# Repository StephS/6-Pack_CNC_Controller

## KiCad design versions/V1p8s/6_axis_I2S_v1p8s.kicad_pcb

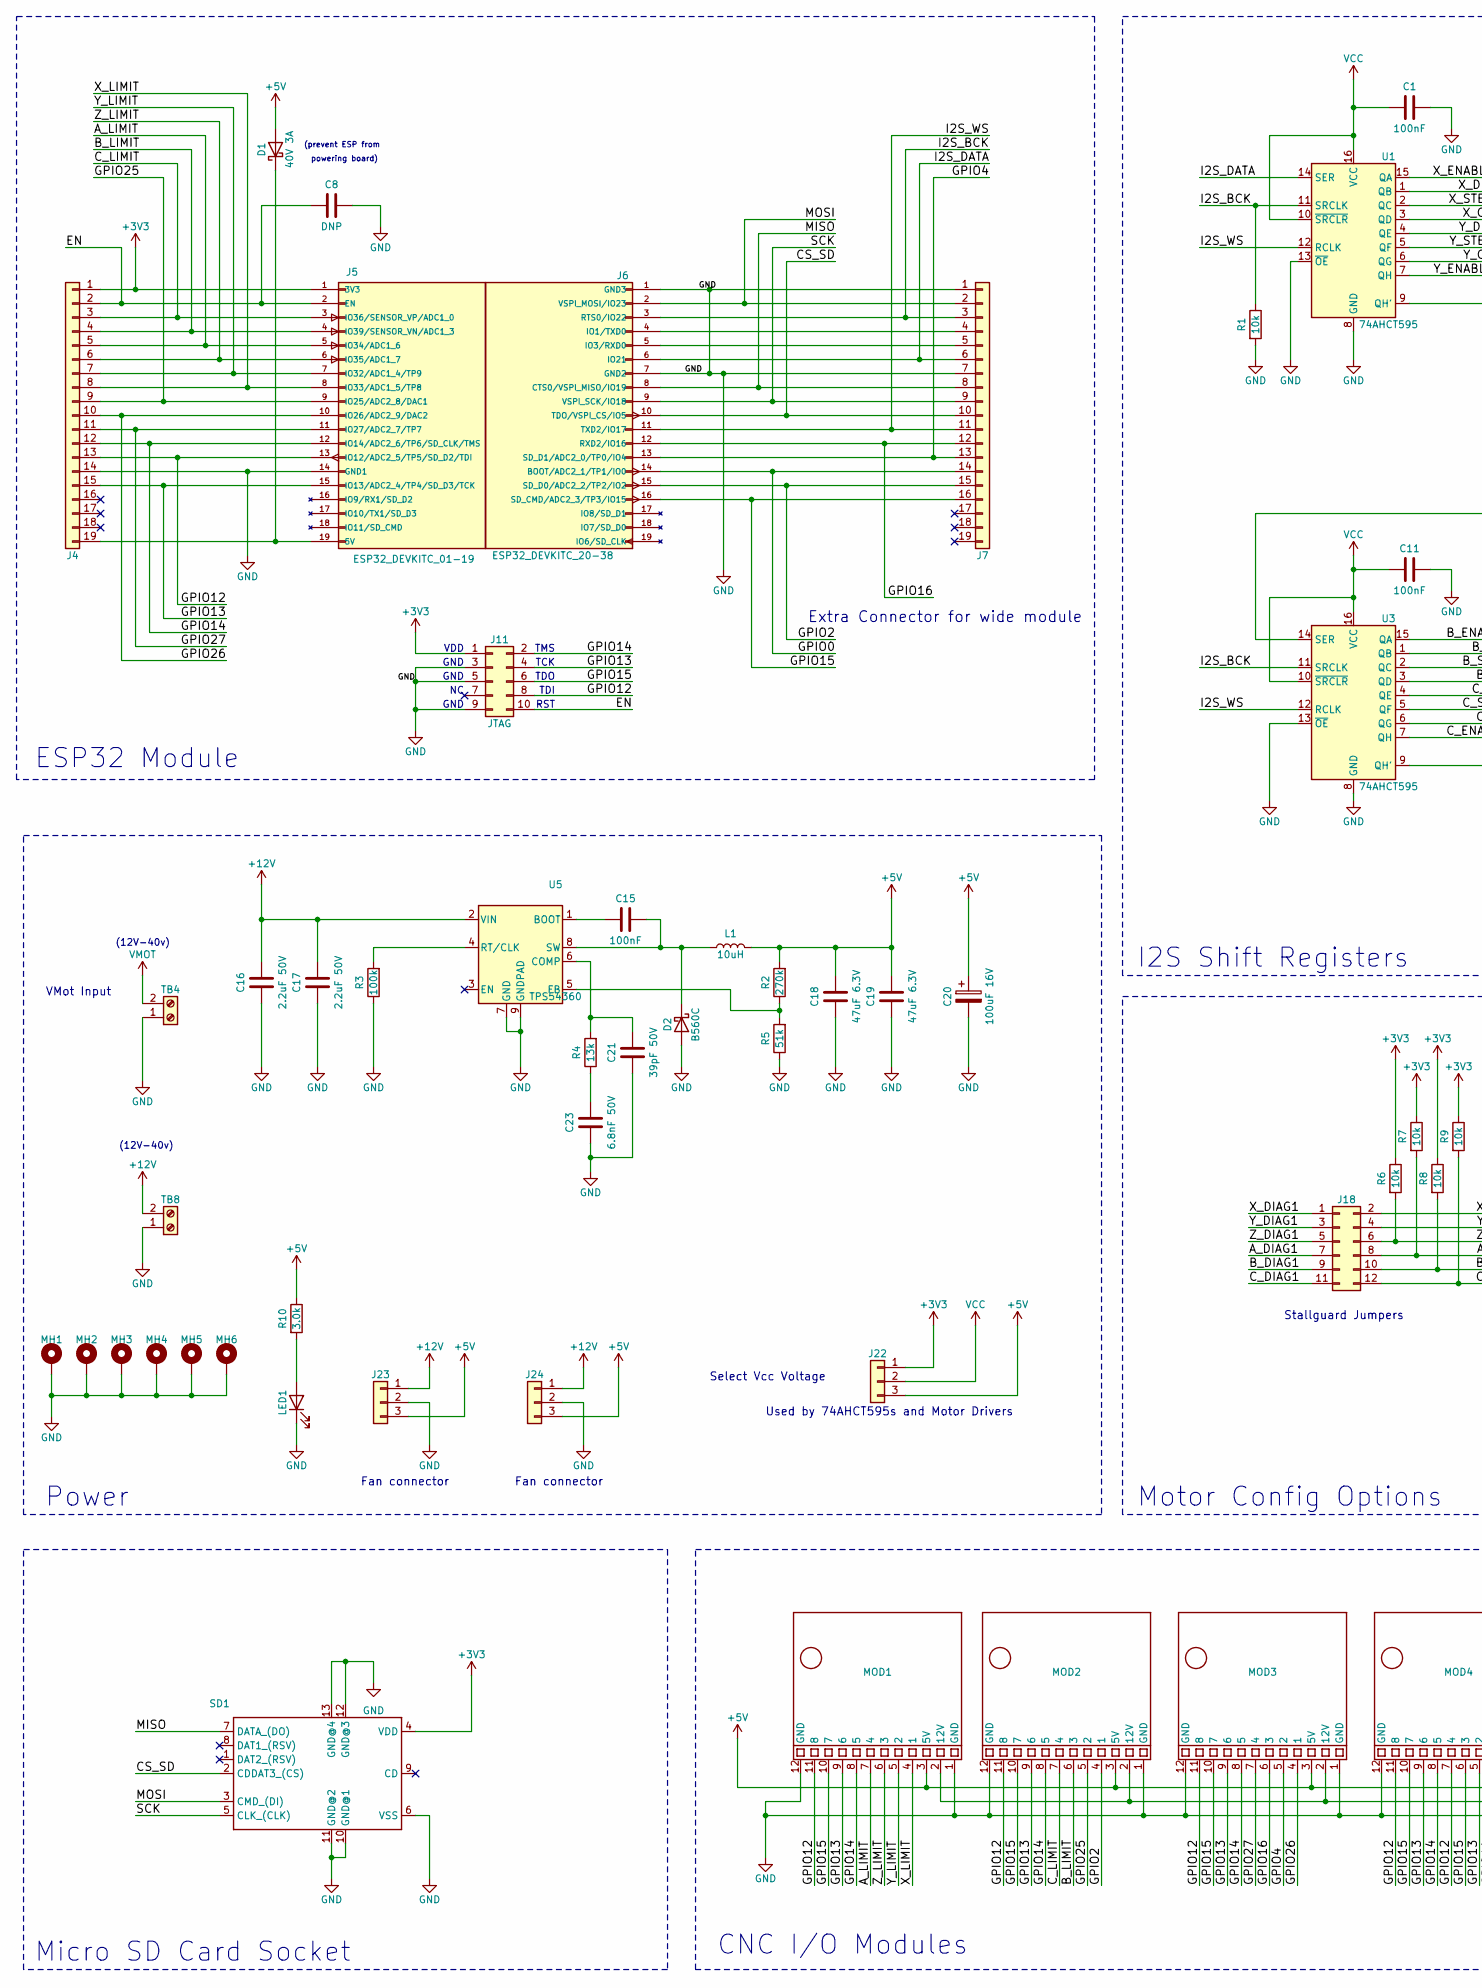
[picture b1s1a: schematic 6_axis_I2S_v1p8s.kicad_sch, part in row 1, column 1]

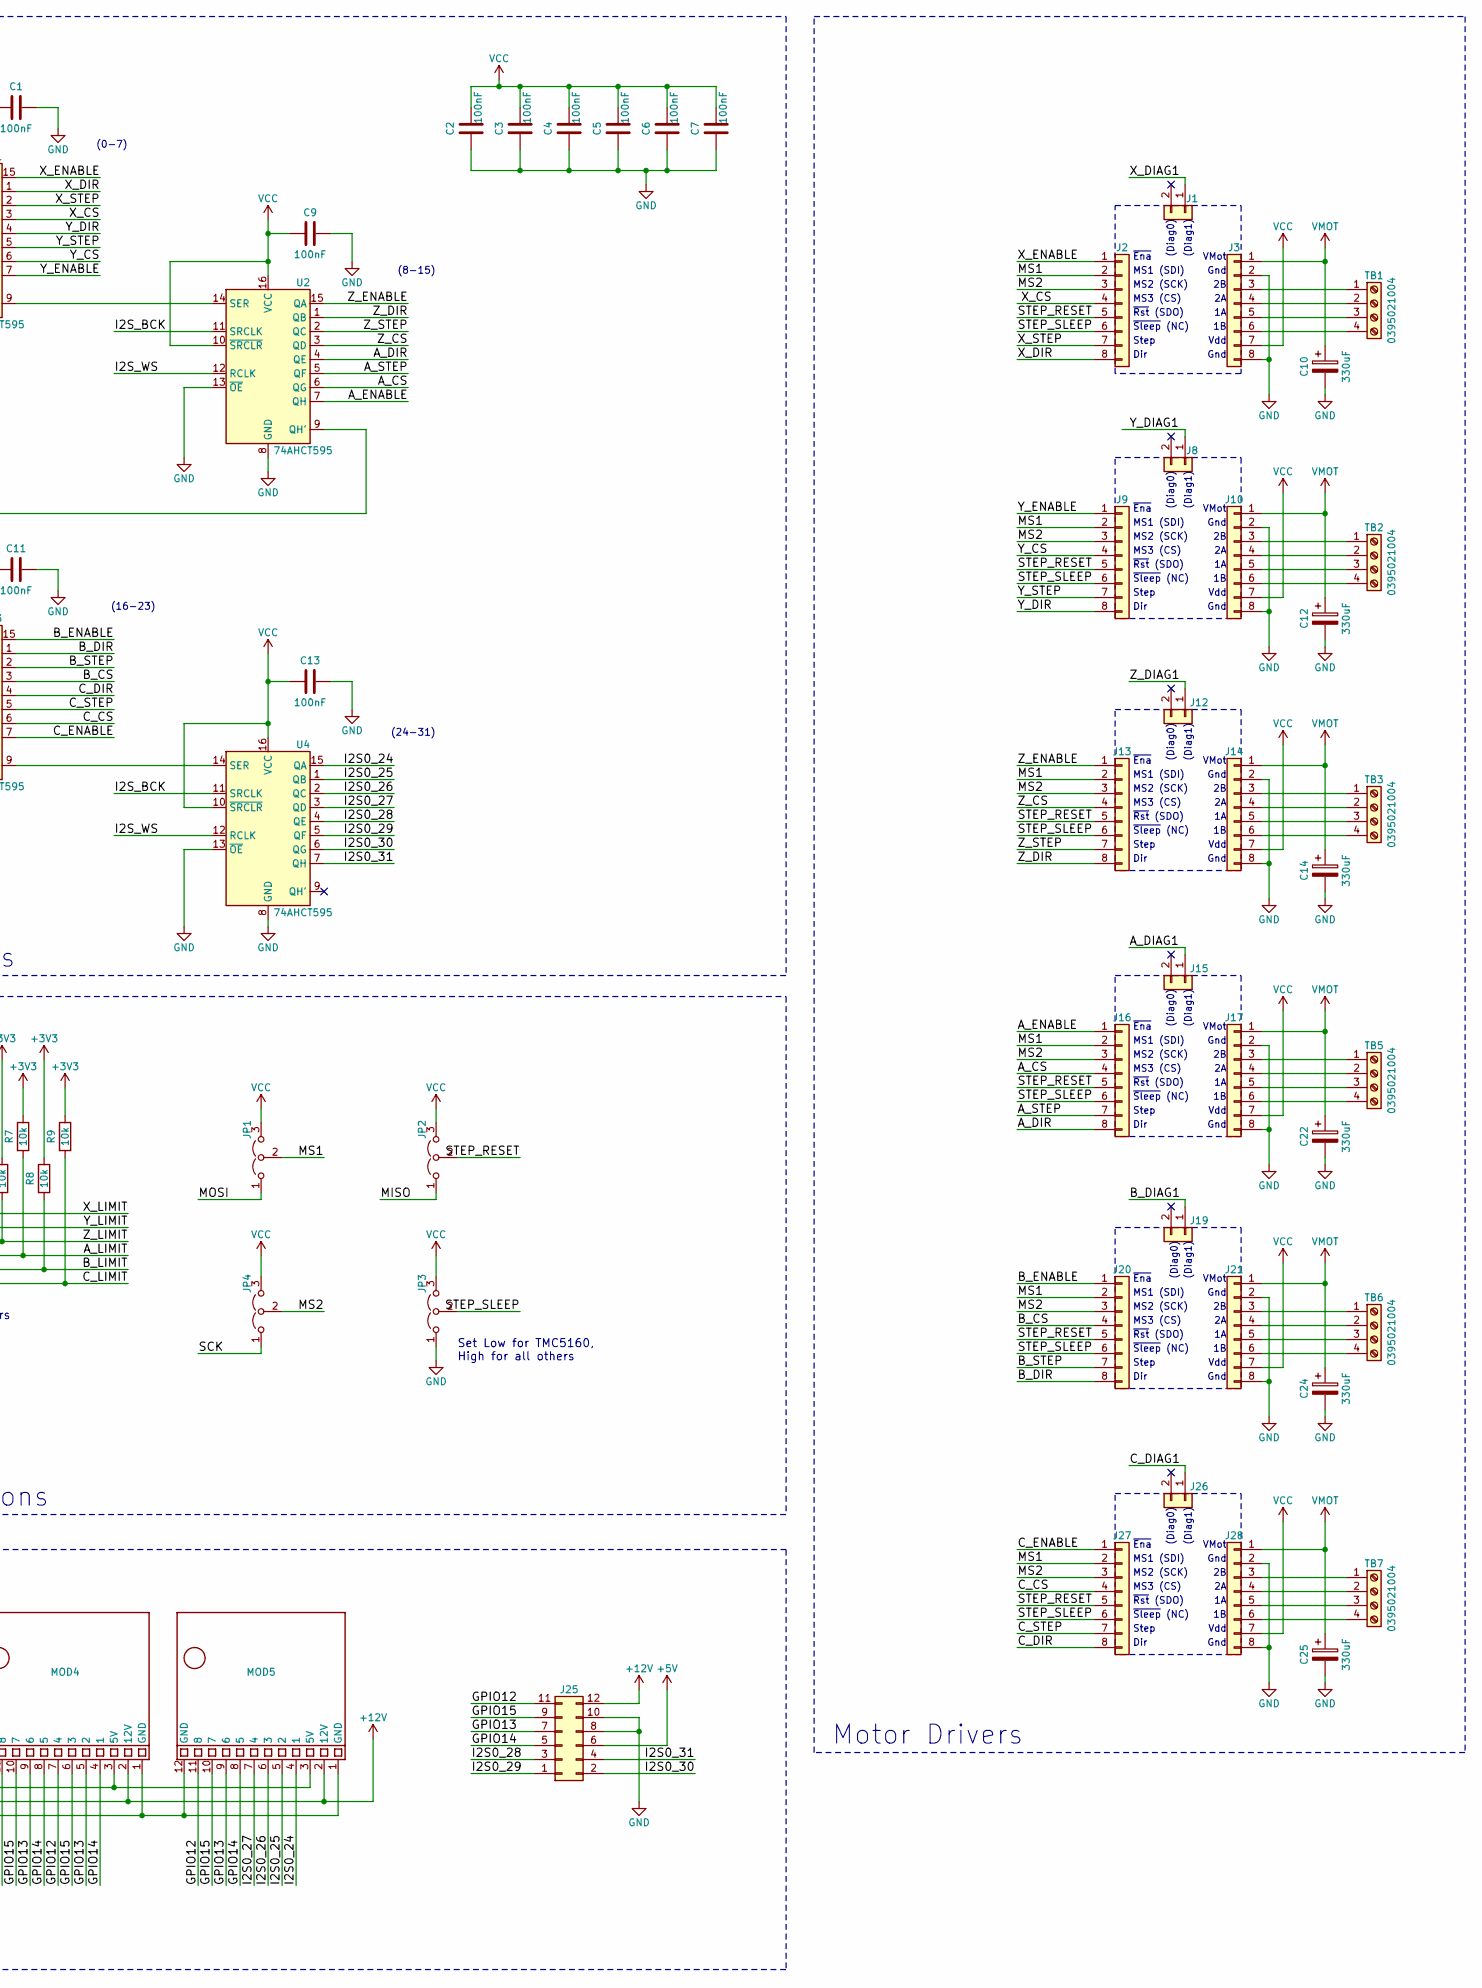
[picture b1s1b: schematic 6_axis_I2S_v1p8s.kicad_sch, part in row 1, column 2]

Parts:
C1, C2, C3, C4, C5, C6, C7, C9, C11, C13, C15: 100nF; C_0402_1005Metric_Pad0.74x0.62mm_HandSolder
C8: DNP; C_1206_3216Metric_Pad1.42x1.75mm_HandSolder
C10, C12, C14, C22, C24, C25: 330uF; C_Elec_10x10.2
C16, C17: 2.2uF 50V; C_0805_2012Metric
C18, C19: 47uF 6.3V; C_0805_2012Metric
C20: 100uF 16V; CP_Elec_6.3x9.9
C21: 39pF 50V; C_0402_1005Metric
C23: 6.8nF 50V; C_0402_1005Metric
D1: 40V 3A; D_SMA
D2: B560C; D_SMC
J1, J8, J12, J15, J19, J26: 2 Pos; PinSocket_1x02_P2.54mm_Vertical
J2, J3, J9, J10, J13, J14, J16, J17, J20, J21, J27, J28: 8S; PinSocket_1x08_P2.54mm_Vertical
J4, J7: 19S; PinSocket_1x19_P2.54mm_Vertical
J5: ESP32_DEVKITC_01-19; PinSocket_1x19_P2.54mm_Vertical
J6: ESP32_DEVKITC_20-38; PinSocket_1x19_P2.54mm_Vertical
J11: JTAG; IDC-Header_2x05_P2.54mm_Vertical
J18: 6S; PinHeader_2x06_P2.54mm_Vertical
J22, J23, J24: 3P; PinHeader_1x03_P2.54mm_Vertical
J25: 6S; PinSocket_2x06_P2.54mm_Horizontal
JP1, JP2, JP3, JP4: 3P; PinHeader_1x03_P2.54mm_Vertical
L1: 10uH; L_Sunlord_MWSA0503_5.4x5.2mm; Part N MWSA0503S-100MT
LED1: GRN; LED_0805_2012Metric_Castellated
MH1, MH2, MH3, MH4, MH5, MH6: MOUNTING_HOLE_M3.7; MountingHole_3.5mm_Pad_TopBottom
MOD1, MOD2, MOD3, MOD4, MOD5: 1x12 Socket; CNC_ModuleSocket_1x12_P2.54mm
R1, R6, R7, R8, R9: 10k; R_0402_1005Metric
R2: 270k; R_0402_1005Metric
R3: 100k; R_0402_1005Metric
R4: 13k; R_0402_1005Metric
R5: 51k; R_0402_1005Metric
R10: 3.0k; R_0603_1608Metric_Pad0.98x0.95mm_HandSolder
SD1: Micro SD; HRO_ELEC-TF-01A
TB1, TB2, TB3, TB5, TB6, TB7: 0395021004; TerminalBlock_Molex_0395021004_1x04_P3.50mm_Horizontal
TB4, TB8: 2 Pos; TerminalBlock_Phoenix_MKDS-1,5-2_1x02_P5.00mm_Horizontal
U1, U2, U3, U4: 74AHCT595; SOIC-16_3.9x9.9mm_P1.27mm
U5: TPS54360; TI_SO-PowerPAD-8

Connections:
+3V3: J4.1, J5.1 (3V3), J11.1, J22.1, R6.1, R7.1, R8.1, R9.1, SD1.4 (VDD)
+5V: C18.2, C19.2, C20.1, D1.2 (A), J22.3, J23.3, J24.3, J25.6, L1.2, MOD1.3 (5V), MOD2.3 (5V), MOD3.3 (5V), MOD4.3 (5V), MOD5.3 (5V), R2.2, R10.1
+12V: C16.2, C17.2, J23.1, J24.1, J25.12, MOD1.2 (12V), MOD2.2 (12V), MOD3.2 (12V), MOD4.2 (12V), MOD5.2 (12V), TB8.2, U5.2 (VIN)
/A_CS: J16.4, U2.6 (QG)
/A_DIAG1: J15.1, J18.7
/A_DIR: J16.8, U2.4 (QE)
/A_ENABLE: J16.1, U2.7 (QH)
/A_LIMIT: J4.5, J5.5 (IO34/ADC1_6), J18.8, MOD1.7 (4), R7.2
/A_STEP: J16.7, U2.5 (QF)
/B_CS: J20.4, U3.3 (QD)
/B_DIAG1: J18.9, J19.1
/B_DIR: J20.8, U3.1 (QB)
/B_ENABLE: J20.1, U3.15 (QA)
/B_LIMIT: J4.4, J5.4 (IO39/SENSOR_VN/ADC1_3), J18.10, MOD2.6 (3), R8.2
/B_STEP: J20.7, U3.2 (QC)
/CS_SD: J6.10 (TDO/VSPI_CS/IO5), J7.10, SD1.2 (CDDAT3_(CS))
/C_CS: J27.4, U3.6 (QG)
/C_DIAG1: J18.11, J26.1
/C_DIR: J27.8, U3.4 (QE)
/C_ENABLE: J27.1, U3.7 (QH)
/C_LIMIT: J4.3, J5.3 (IO36/SENSOR_VP/ADC1_0), J18.12, MOD2.7 (4), R9.2
/C_STEP: J27.7, U3.5 (QF)
/EN: C8.1, J4.2, J5.2 (EN), J11.10
/GPIO0: J6.14 (BOOT/ADC2_1/TP1/IO0), J7.14
/GPIO2: J6.15 (SD_D0/ADC2_2/TP2/IO2), J7.15, MOD2.4 (1)
/GPIO4: J6.13 (SD_D1/ADC2_0/TP0/IO4), J7.13, MOD3.5 (2)
/GPIO12: J4.13, J5.13 (IO12/ADC2_5/TP5/SD_D2/TDI), J11.8, J25.11, MOD1.11 (8), MOD2.11 (8), MOD3.11 (8), MOD4.7 (4), MOD4.11 (8), MOD5.11 (8)
/GPIO13: J4.15, J5.15 (IO13/ADC2_4/TP4/SD_D3/TCK), J11.4, J25.7, MOD1.9 (6), MOD2.9 (6), MOD3.9 (6), MOD4.5 (2), MOD4.9 (6), MOD5.9 (6)
/GPIO14: J4.12, J5.12 (IO14/ADC2_6/TP6/SD_CLK/TMS), J11.2, J25.5, MOD1.8 (5), MOD2.8 (5), MOD3.8 (5), MOD4.4 (1), MOD4.8 (5), MOD5.8 (5)
/GPIO15: J6.16 (SD_CMD/ADC2_3/TP3/IO15), J7.16, J11.6, J25.9, MOD1.10 (7), MOD2.10 (7), MOD3.10 (7), MOD4.6 (3), MOD4.10 (7), MOD5.10 (7)
/GPIO16: J6.12 (RXD2/IO16), J7.12, MOD3.6 (3)
/GPIO25: J4.9, J5.9 (IO25/ADC2_8/DAC1), MOD2.5 (2)
/GPIO26: J4.10, J5.10 (IO26/ADC2_9/DAC2), MOD3.4 (1)
/GPIO27: J4.11, J5.11 (IO27/ADC2_7/TP7), MOD3.7 (4)
/I2S0_24: MOD5.4 (1), U4.15 (QA)
/I2S0_25: MOD5.5 (2), U4.1 (QB)
/I2S0_26: MOD5.6 (3), U4.2 (QC)
/I2S0_27: MOD5.7 (4), U4.3 (QD)
/I2S0_28: J25.3, U4.4 (QE)
/I2S0_29: J25.1, U4.5 (QF)
/I2S0_30: J25.2, U4.6 (QG)
/I2S0_31: J25.4, U4.7 (QH)
/I2S_BCK: J6.3 (RTS0/IO22), J7.3, R1.1, U1.11 (SRCLK), U2.11 (SRCLK), U3.11 (SRCLK), U4.11 (SRCLK)
/I2S_DATA: J6.6 (IO21), J7.6, U1.14 (SER)
/I2S_WS: J6.11 (TXD2/IO17), J7.11, U1.12 (RCLK), U2.12 (RCLK), U3.12 (RCLK), U4.12 (RCLK)
/MISO: J6.8 (CTS0/VSPI_MISO/IO19), J7.8, JP2.1 (A), SD1.7 (DATA_(DO))
/MOSI: J6.2 (VSPI_MOSI/IO23), J7.2, JP1.1 (A), SD1.3 (CMD_(DI))
/MS1: J2.2, J9.2, J13.2, J16.2, J20.2, J27.2, JP1.2 (C)
/MS2: J2.3, J9.3, J13.3, J16.3, J20.3, J27.3, JP4.2 (C)
/SCK: J6.9 (VSPI_SCK/IO18), J7.9, JP4.1 (A), SD1.5 (CLK_(CLK))
/STEP_RESET: J2.5, J9.5, J13.5, J16.5, J20.5, J27.5, JP2.2 (C)
/STEP_SLEEP: J2.6, J9.6, J13.6, J16.6, J20.6, J27.6, JP3.2 (C)
/X_CS: J2.4, U1.3 (QD)
/X_DIAG1: J1.1, J18.1
/X_DIR: J2.8, U1.1 (QB)
/X_ENABLE: J2.1, U1.15 (QA)
/X_LIMIT: J4.8, J5.8 (IO33/ADC1_5/TP8), J18.2, MOD1.4 (1)
/X_STEP: J2.7, U1.2 (QC)
/Y_CS: J9.4, U1.6 (QG)
/Y_DIAG1: J8.1, J18.3
/Y_DIR: J9.8, U1.4 (QE)
/Y_ENABLE: J9.1, U1.7 (QH)
/Y_LIMIT: J4.7, J5.7 (IO32/ADC1_4/TP9), J18.4, MOD1.5 (2)
/Y_STEP: J9.7, U1.5 (QF)
/Z_CS: J13.4, U2.3 (QD)
/Z_DIAG1: J12.1, J18.5
/Z_DIR: J13.8, U2.1 (QB)
/Z_ENABLE: J13.1, U2.15 (QA)
/Z_LIMIT: J4.6, J5.6 (IO35/ADC1_7), J18.6, MOD1.6 (3), R6.2
/Z_STEP: J13.7, U2.2 (QC)
GND: C1.2, C2.1, C3.1, C4.1, C5.1, C6.1, C7.1, C8.2, C9.2, C10.2, C11.2, C12.2, C13.2, C14.2, C16.1, C17.1, C18.1, C19.1, C20.2, C21.1, C22.2, C23.1, C24.2, C25.2, D2.2 (A), J3.2, J3.8, J4.14, J5.14 (GND1), J6.1 (GND3), J6.7 (GND2), J7.1, J7.7, J10.2, J10.8, J11.3, J11.5, J11.9, J14.2, J14.8, J17.2, J17.8, J21.2, J21.8, J23.2, J24.2, J25.8, J25.10, J28.2, J28.8, JP3.1 (A), LED1.1 (K), MH1.1, MH2.1, MH3.1, MH4.1, MH5.1, MH6.1, MOD1.1 (GND), MOD1.12 (GND), MOD2.1 (GND), MOD2.12 (GND), MOD3.1 (GND), MOD3.12 (GND), MOD4.1 (GND), MOD4.12 (GND), MOD5.1 (GND), MOD5.12 (GND), R1.2, R3.1, R5.1, SD1.6 (VSS), SD1.10 (GND@1), SD1.11 (GND@2), SD1.12 (GND@3), SD1.13 (GND@4), TB4.1, TB8.1, U1.8 (GND), U1.13 (~OE), U2.8 (GND), U2.13 (~OE), U3.8 (GND), U3.13 (~OE), U4.8 (GND), U4.13 (~OE), U5.7 (GND), U5.9 (GNDPAD)
unnamed: C15.1, U5.1 (BOOT)
unnamed: C15.2, D2.1 (K), L1.1, U5.8 (SW)
unnamed: C21.2, R4.2, U5.6 (COMP)
unnamed: C23.2, R4.1
unnamed: D1.1 (K), J4.19, J5.19 (5V)
unnamed: J3.3, TB1.1
unnamed: J3.4, TB1.2
unnamed: J3.5, TB1.3
unnamed: J3.6, TB1.4
unnamed: J6.4 (IO1/TXD0), J7.4
unnamed: J6.5 (IO3/RXD0), J7.5
unnamed: J10.3, TB2.1
unnamed: J10.4, TB2.2
unnamed: J10.5, TB2.3
unnamed: J10.6, TB2.4
unnamed: J14.3, TB3.1
unnamed: J14.4, TB3.2
unnamed: J14.5, TB3.3
unnamed: J14.6, TB3.4
unnamed: J17.3, TB5.1
unnamed: J17.4, TB5.2
unnamed: J17.5, TB5.3
unnamed: J17.6, TB5.4
unnamed: J21.3, TB6.1
unnamed: J21.4, TB6.2
unnamed: J21.5, TB6.3
unnamed: J21.6, TB6.4
unnamed: J28.3, TB7.1
unnamed: J28.4, TB7.2
unnamed: J28.5, TB7.3
unnamed: J28.6, TB7.4
unnamed: LED1.2 (A), R10.2
unnamed: R2.1, R5.2, U5.5 (FB)
unnamed: R3.2, U5.4 (RT/CLK)
unnamed: U1.9 (QH'), U2.14 (SER)
unnamed: U2.9 (QH'), U3.14 (SER)
unnamed: U3.9 (QH'), U4.14 (SER)
VCC: C1.1, C2.2, C3.2, C4.2, C5.2, C6.2, C7.2, C9.1, C11.1, C13.1, J3.7, J10.7, J14.7, J17.7, J21.7, J22.2, J28.7, JP1.3 (B), JP2.3 (B), JP3.3 (B), JP4.3 (B), U1.10 (~SRCLR), U1.16 (VCC), U2.10 (~SRCLR), U2.16 (VCC), U3.10 (~SRCLR), U3.16 (VCC), U4.10 (~SRCLR), U4.16 (VCC)
VMOT: C10.1, C12.1, C14.1, C22.1, C24.1, C25.1, J3.1, J10.1, J14.1, J17.1, J21.1, J28.1, TB4.2

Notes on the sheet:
Stallguard Jumpers
VMot
MS3 (CS)
TDO
~{Sleep} (NC)
MS1 (SDI)
(12V-40v)
MS2 (SCK)
~{Ena}
GND
~{Rst} (SDO)
Dir
Step
Gnd
(Diag0)
(Diag1)
(prevent ESP from
TMS
Vdd
Extra Connector for wide module
ESP32 Module
(16-23)
Select Vcc Voltage
(0-7)
Power
RST
Micro SD Card Socket
Used by 74AHCT595s and Motor Drivers
powering board)
I2S Shift Registers
(8-15)
TCK
Fan connector
Motor Drivers
(24-31)
TDI
Motor Config Options
VDD
Set Low for TMC5160, High for all others
CNC I/O Modules

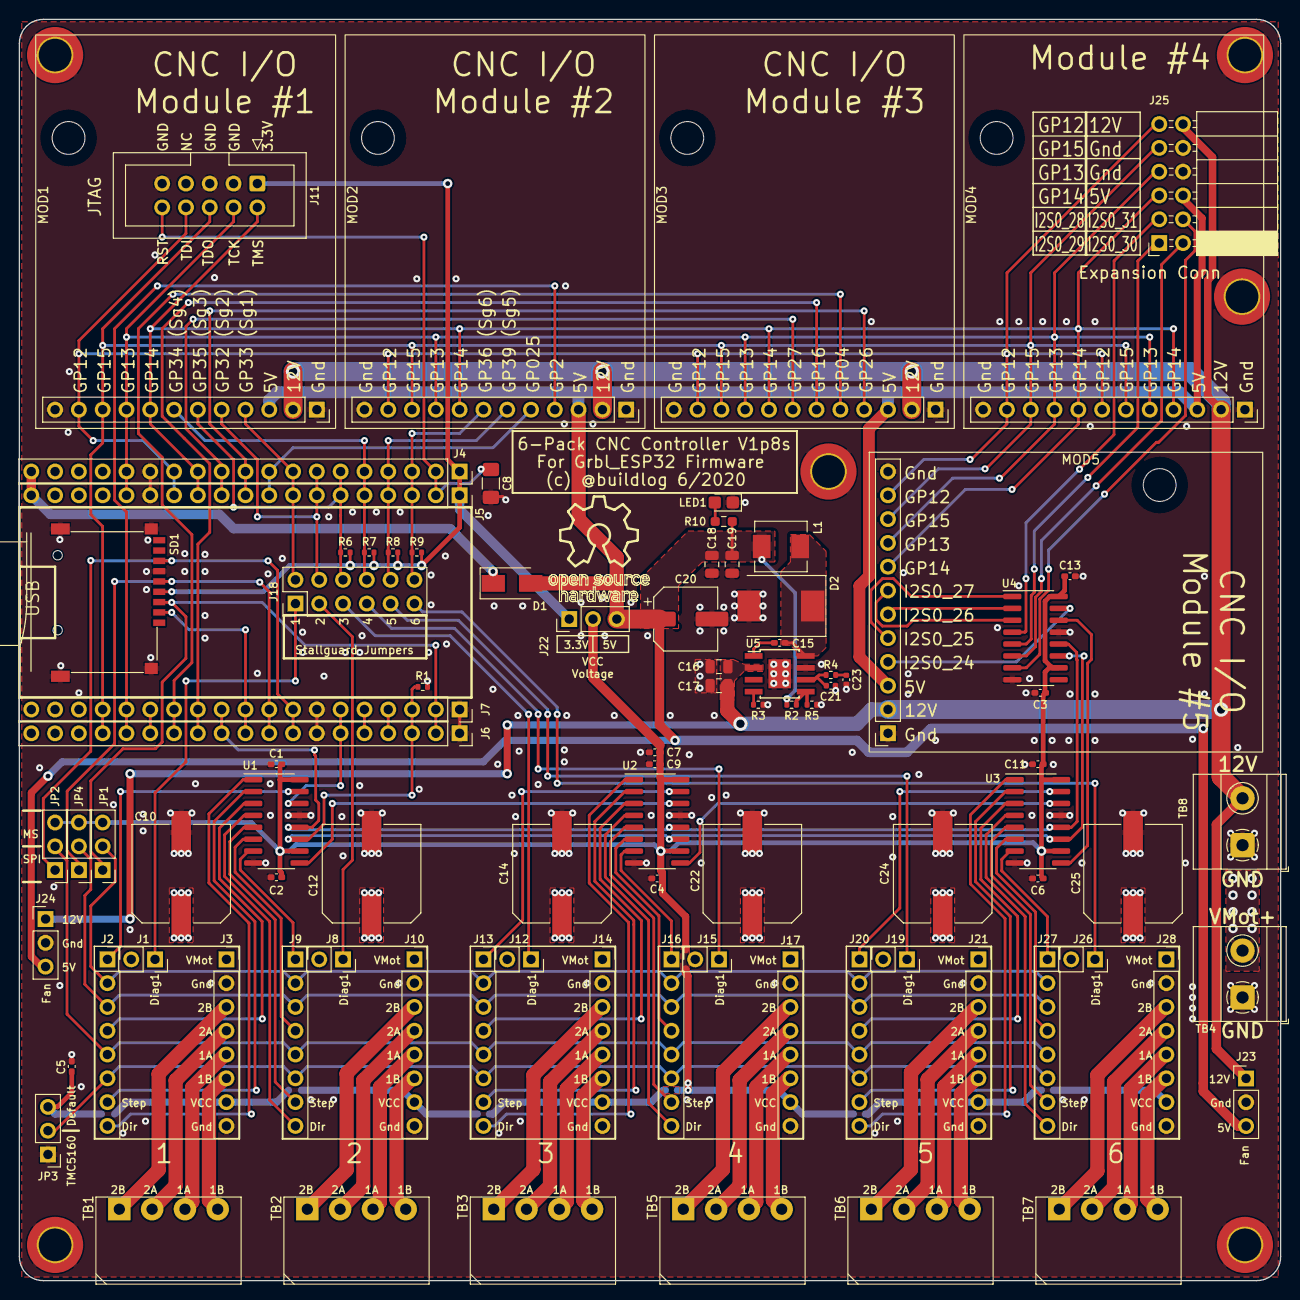
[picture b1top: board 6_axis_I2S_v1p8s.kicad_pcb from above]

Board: 2 copper layers, 134.6 x 134.6 mm, 96 parts (0 on the bottom side), 110 nets.

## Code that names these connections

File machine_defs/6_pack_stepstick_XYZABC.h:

#pragma once
// clang-format off

/*
    6_pack_stepstick_v1.h

    Covers all V1 versions V1p0, V1p1, etc

    Part of Grbl_ESP32
    Pin assignments for the ESP32 I2S 6-axis board
    
    2021-07-31 For Matthew Winchell

    Grbl_ESP32 is free software: you can redistribute it and/or modify
    it under the terms of the GNU General Public License as published by
    the Free Software Foundation, either version 3 of the License, or
    (at your option) any later version.
    Grbl is distributed in the hope that it will be useful,
    but WITHOUT ANY WARRANTY; without even the implied warranty of
    MERCHANTABILITY or FITNESS FOR A PARTICULAR PURPOSE.  See the
    GNU General Public License for more details.
    You should have received a copy of the GNU General Public License
    along with Grbl_ESP32.  If not, see <http://www.gnu.org/licenses/>.
*/
#define MACHINE_NAME            "6 Pack Stepstick XYZABC"

#define N_AXIS 6

// === Special Features

// I2S (steppers & other output-only pins)
#define USE_I2S_OUT
#define USE_I2S_STEPS
//#define DEFAULT_STEPPER ST_I2S_STATIC

#define USE_STEPSTICK   // makes sure MS1,2,3 !reset and !sleep are set

#define I2S_OUT_BCK             GPIO_NUM_22
#define I2S_OUT_WS              GPIO_NUM_17
#define I2S_OUT_DATA            GPIO_NUM_21


// Motor Socket #1
#define X_DISABLE_PIN           I2SO(0)
#define X_DIRECTION_PIN         I2SO(1)
#define X_STEP_PIN              I2SO(2)
#define X_STEPPER_MS3           I2SO(3)

// Motor Socket #2
#define Y_DIRECTION_PIN         I2SO(4)
#define Y_STEP_PIN              I2SO(5)
#define Y_STEPPER_MS3           I2SO(6)
#define Y_DISABLE_PIN           I2SO(7)

// Motor Socket #3
#define Z_DISABLE_PIN           I2SO(8)
#define Z_DIRECTION_PIN         I2SO(9)
#define Z_STEP_PIN              I2SO(10)
#define Z_STEPPER_MS3           I2SO(11)

// Motor Socket #4
#define A_DIRECTION_PIN         I2SO(12)
#define A_STEP_PIN              I2SO(13)
#define A_STEPPER_MS3           I2SO(14) 
#define A_DISABLE_PIN           I2SO(15)

// Motor Socket #5
#define B_DISABLE_PIN           I2SO(16)
#define B_DIRECTION_PIN         I2SO(17)
#define B_STEP_PIN              I2SO(18)
#define B_STEPPER_MS3           I2SO(19) 

// Motor Socket #5
#define C_DIRECTION_PIN         I2SO(20)
#define C_STEP_PIN              I2SO(21)
#define C_STEPPER_MS3           I2SO(22)
#define C_DISABLE_PIN           I2SO(23)


/*
    Socket I/O reference
    The list of modules is here...
    https://github.com/bdring/6-Pack_CNC_Controller/wiki/CNC-I-O-Module-List
    Click on each module to get example for using the modules in the sockets


Socket #1
#1 GPIO_NUM_33 
#2 GPIO_NUM_32
#3 GPIO_NUM_35 (input only)
#4 GPIO_NUM_34 (input only)

Socket #2
#1 GPIO_NUM_2
#2 GPIO_NUM_25
#3 GPIO_NUM_39 (input only)
#4 GPIO_NUM_36 (input only)

Socket #3
#1 GPIO_NUM_26
#2 GPIO_NUM_4
#3 GPIO_NUM_16
#4 GPIO_NUM_27

Socket #4
#1 GPIO_NUM_14
#2 GPIO_NUM_13
#3 GPIO_NUM_15
#4 GPIO_NUM_12

Socket #5
#1 I2SO(24)  (output only)
#2 I2SO(25)  (output only)
#3 I2SO26)  (output only)

*/

// 4x Input Module in Socket #1
// https://github.com/bdring/6-Pack_CNC_Controller/wiki/4x-Switch-Input-module
#define X_LIMIT_PIN             GPIO_NUM_33
#define Y_LIMIT_PIN             GPIO_NUM_32
#define Z_LIMIT_PIN             GPIO_NUM_35
#define A_LIMIT_PIN             GPIO_NUM_34

// 4x Switch Input module  in socket #2
// // https://github.com/bdring/6-Pack_CNC_Controller/wiki/4x-Switch-Input-module
#define B_LIMIT_PIN           GPIO_NUM_2
#define C_LIMIT_PIN           GPIO_NUM_25
//#define MACRO_BUTTON_1_PIN    GPIO_NUM_39
//#define MACRO_BUTTON_2_PIN    GPIO_NUM_36


// === Default settings
#define DEFAULT_STEP_PULSE_MICROSECONDS I2S_OUT_USEC_PER_PULSE

#define DEFAULT_INVERT_LIMIT_PINS       0
#define DEFAULT_INVERT_PROBE_PIN        0

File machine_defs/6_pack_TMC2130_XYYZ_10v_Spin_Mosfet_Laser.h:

#pragma once
// clang-format off

/*
    6_pack_TMC2130_XYYZ_10v_Spin_Mosfet_Laser.h

    Part of Grbl_ESP32
    Pin assignments for the ESP32 SPI 6-axis board

    2021-06-06 B. Dring for Omar Abo-Namous

    Grbl_ESP32 is free software: you can redistribute it and/or modify
    it under the terms of the GNU General Public License as published by
    the Free Software Foundation, either version 3 of the License, or
    (at your option) any later version.
    Grbl is distributed in the hope that it will be useful,
    but WITHOUT ANY WARRANTY; without even the implied warranty of
    MERCHANTABILITY or FITNESS FOR A PARTICULAR PURPOSE.  See the
    GNU General Public License for more details.
    You should have received a copy of the GNU General Public License
    along with Grbl_ESP32.  If not, see <http://www.gnu.org/licenses/>.
*/
#define MACHINE_NAME            "6 Pack TMC2130 XYYZ 10V spin FET Laser"

#define N_AXIS 3

// I2S (steppers & other output-only pins)
#define USE_I2S_OUT
#define USE_I2S_STEPS
//#define DEFAULT_STEPPER ST_I2S_STATIC

#define I2S_OUT_BCK      GPIO_NUM_22
#define I2S_OUT_WS       GPIO_NUM_17
#define I2S_OUT_DATA     GPIO_NUM_21

#define TRINAMIC_RUN_MODE           Motors::TrinamicMode::StealthChop
#define TRINAMIC_HOMING_MODE        Motors::TrinamicMode::StealthChop

// Motor Socket #1
#define X_TRINAMIC_DRIVER       2130
#define X_DISABLE_PIN           I2SO(0)
#define X_DIRECTION_PIN         I2SO(1)
#define X_STEP_PIN              I2SO(2)
#define X_CS_PIN                I2SO(3)
#define X_RSENSE                TMC2130_RSENSE_DEFAULT

// Motor Socket #2
#define Y_TRINAMIC_DRIVER       X_TRINAMIC_DRIVER
#define Y_DIRECTION_PIN         I2SO(4)
#define Y_STEP_PIN              I2SO(5)
#define Y_DISABLE_PIN           I2SO(7)
#define Y_CS_PIN                I2SO(6)
#define Y_RSENSE                X_RSENSE

// Motor Socket #3
#define Y2_TRINAMIC_DRIVER       X_TRINAMIC_DRIVER
#define Y2_DISABLE_PIN           I2SO(8)
#define Y2_DIRECTION_PIN         I2SO(9)
#define Y2_STEP_PIN              I2SO(10)
#define Y2_CS_PIN                I2SO(11)
#define Y2_RSENSE                X_RSENSE

// Motor Socket #4
#define Z_TRINAMIC_DRIVER       X_TRINAMIC_DRIVER
#define Z_DIRECTION_PIN         I2SO(12)
#define Z_STEP_PIN              I2SO(13)
#define Z_DISABLE_PIN           I2SO(15)
#define Z_CS_PIN                I2SO(14)
#define Z_RSENSE                X_RSENSE



/*
    Socket I/O reference
    The list of modules is here...
    https://github.com/bdring/6-Pack_CNC_Controller/wiki/CNC-I-O-Module-List
    Click on each module to get example for using the modules in the sockets

Socket #1
#1 GPIO_NUM_33 (Sg1)
#2 GPIO_NUM_32 (Sg2)
#3 GPIO_NUM_35 (Sg3) (input only)
#4 GPIO_NUM_34 (Sg4) (input only)

Socket #2
#1 GPIO_NUM_2
#2 GPIO_NUM_25
#3 GPIO_NUM_39 (Sg5) (input only)
#4 GPIO_NUM_36 (Sg6) (input only)

Socket #3
#1 GPIO_NUM_26
#2 GPIO_NUM_4
#3 GPIO_NUM_16
#4 GPIO_NUM_27

Socket #4
#1 GPIO_NUM_14
#2 GPIO_NUM_13
#3 GPIO_NUM_15
#4 GPIO_NUM_12

Socket #5
#1 I2SO(24)  (output only)
#2 I2SO(25)  (output only)
#3 I2SO26)  (output only)

*/

// 4x Input Module in Socket #1
// https://github.com/bdring/6-Pack_CNC_Controller/wiki/4x-Switch-Input-module
#define X_LIMIT_PIN             GPIO_NUM_33
#define Y_LIMIT_PIN             GPIO_NUM_32
#define Z_LIMIT_PIN             GPIO_NUM_35
#define PROBE_PIN               GPIO_NUM_34



// when used in socket #3
// https://github.com/bdring/6-Pack_CNC_Controller/wiki/0-10V-Output-Module
#define SPINDLE_TYPE            SpindleType::_10V// default, check actual $Spindle/Type Setting
#define SPINDLE_OUTPUT_PIN      GPIO_NUM_26
#define SPINDLE_FORWARD_PIN     GPIO_NUM_4
#define SPINDLE_REVERSE_PIN     GPIO_NUM_16


// Socket #4
// https://github.com/bdring/6-Pack_CNC_Controller/wiki/Quad-MOSFET-Module
#define LASER_OUTPUT_PIN       GPIO_NUM_14
#define COOLANT_FLOOD_PIN      GPIO_NUM_13
#define USER_DIGITAL_PIN_0     GPIO_NUM_15 
#define USER_ANALOG_PIN_0      GPIO_NUM_12 

// Example (4x) 5V Buffer Output on socket #5
// https://github.com/bdring/6-Pack_CNC_Controller/wiki/4x-5V-Buffered-Output-Module
#define COOLANT_MIST_PIN      I2SO(24) 
#define USER_DIGITAL_PIN_1    I2SO(25)
#define USER_DIGITAL_PIN_2    I2SO(26)
#define USER_DIGITAL_PIN_3    I2SO(27)


// === Default settings
#define DEFAULT_STEP_PULSE_MICROSECONDS I2S_OUT_USEC_PER_PULSE

#define DEFAULT_INVERT_LIMIT_PINS       0
#define DEFAULT_INVERT_PROBE_PIN        0

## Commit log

2021-05-27 Port to Kicad - v1p8s
    Initial port to KiCad, board is yet untested. Passes DRC and ERC.
    a 2nd power plug has been added, TB8, that supplies the 5V regulator, fan headers, and all of the CNC Modules.
    some minor connector location changes.
    Lots of trace layout changes.
2021-10-31 layout changes, screw hole placement changes, generate gerbers
2021-12-27 Update to Kicad 6.0 and add Schematic PDF
2021-12-27 Add Interactive BOM and fix worksheet error
